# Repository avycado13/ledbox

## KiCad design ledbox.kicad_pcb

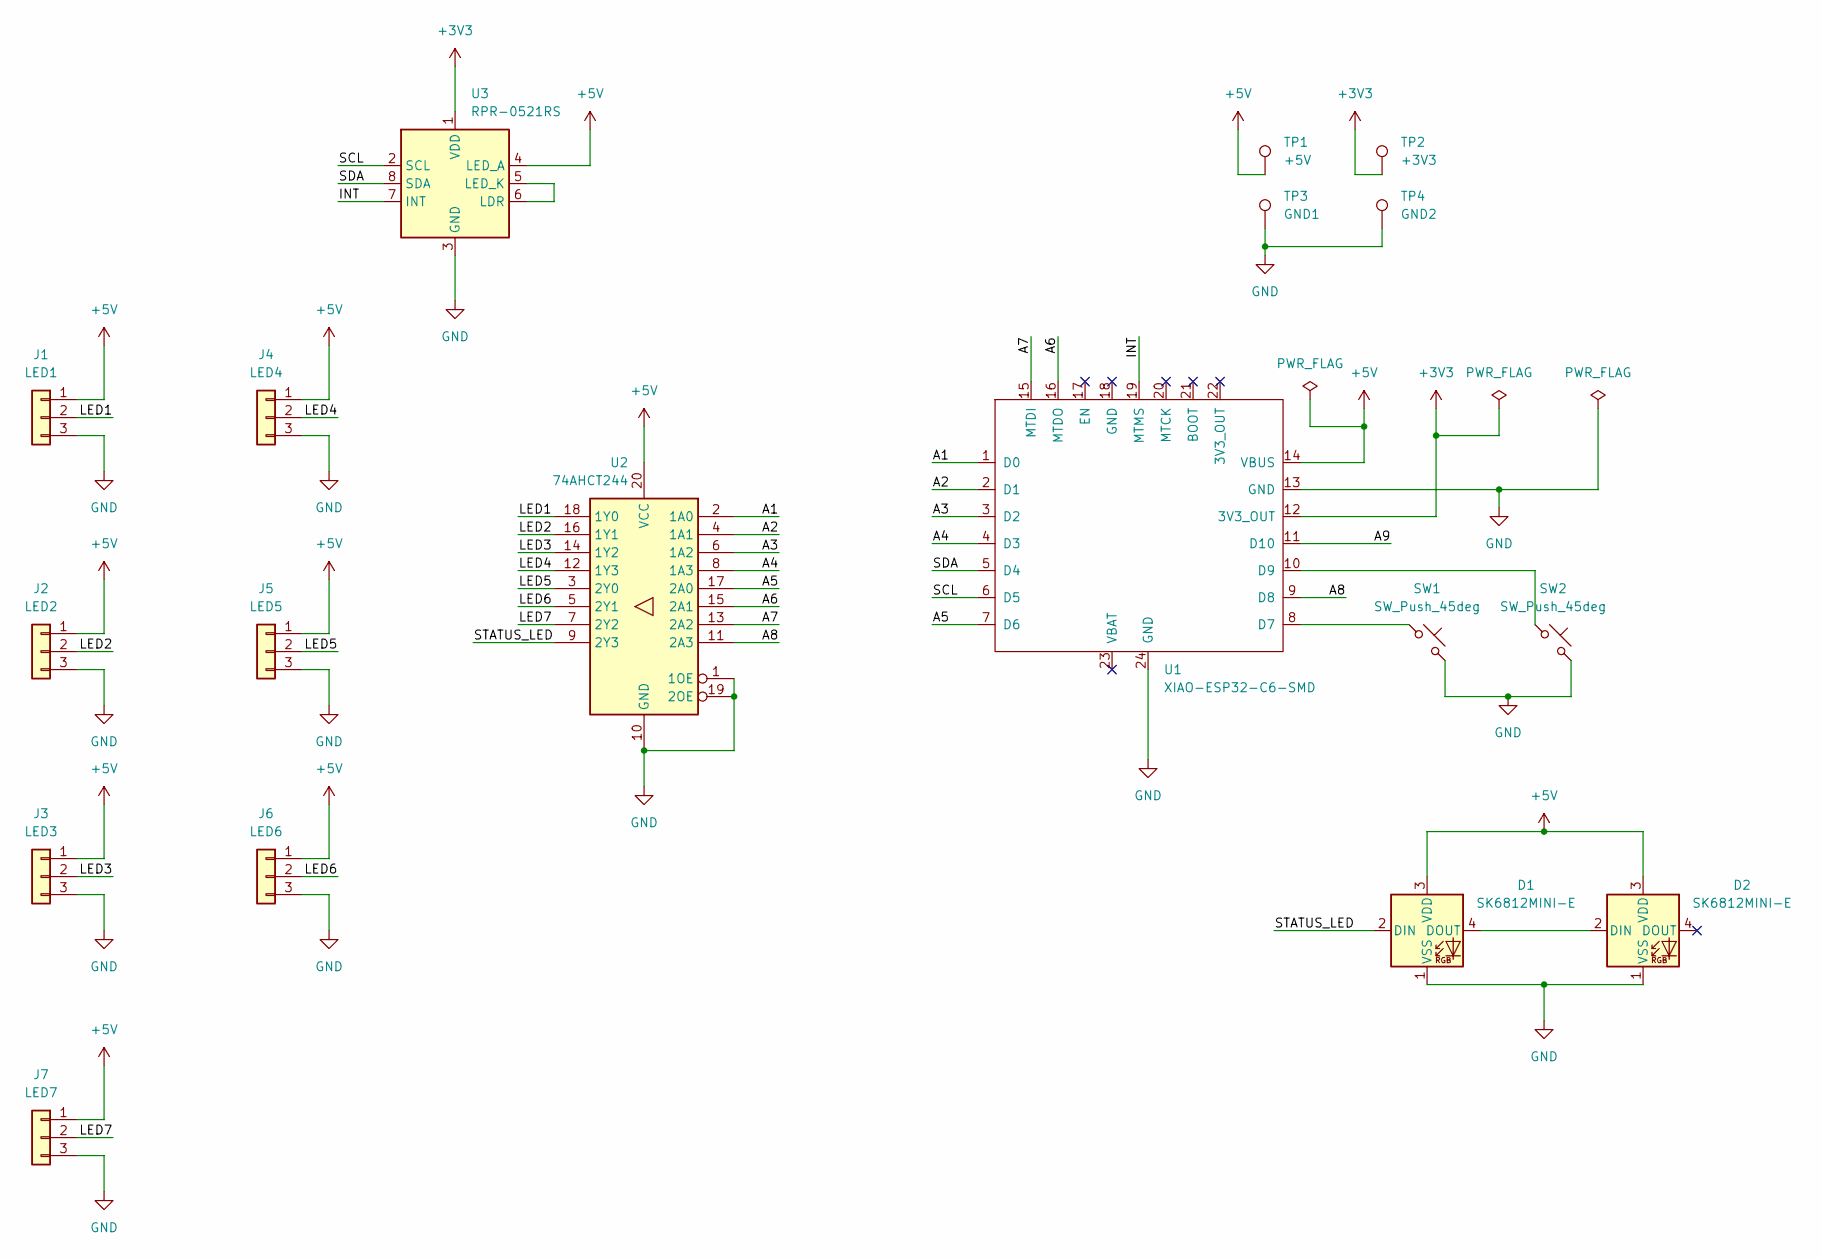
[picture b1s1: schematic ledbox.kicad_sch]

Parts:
D1, D2: SK6812MINI-E; LED_SK6812MINI-E_3.2x2.8mm_P1.5mm_ReverseMount
J1: LED1; PinHeader_1x03_P2.54mm_Horizontal
J2: LED2; PinHeader_1x03_P2.54mm_Horizontal
J3: LED3; PinHeader_1x03_P2.54mm_Horizontal
J4: LED4; PinHeader_1x03_P2.54mm_Horizontal
J5: LED5; PinHeader_1x03_P2.54mm_Horizontal
J6: LED6; PinHeader_1x03_P2.54mm_Horizontal
J7: LED7; PinHeader_1x03_P2.54mm_Horizontal
SW1, SW2: SW_Push_45deg; SW_SPST_PTS645Sx43SMTR92
TP1: +5V; TestPoint_Pad_D4.0mm
TP2: +3V3; TestPoint_Pad_D4.0mm
TP3: GND1; TestPoint_Pad_D4.0mm
TP4: GND2; TestPoint_Pad_D4.0mm
U1: XIAO-ESP32-C6-SMD
U2: 74AHCT244; TSSOP-20_4.4x6.5mm_P0.65mm
U3: RPR-0521RS; Rohm_RPR-0521RS

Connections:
+3V3: TP2.1 (1_1), U1.12 (3V3_OUT), U3.1 (VDD)
+5V: D1.3 (VDD), D2.3 (VDD), J1.1, J2.1, J3.1, J4.1, J5.1, J6.1, J7.1, TP1.1 (1_1), U1.14 (VBUS), U2.20 (VCC), U3.4 (LED_A)
/A1: U1.1 (D0), U2.2 (1A0)
/A2: U1.2 (D1), U2.4 (1A1)
/A3: U1.3 (D2), U2.6 (1A2)
/A4: U1.4 (D3), U2.8 (1A3)
/A5: U1.7 (D6), U2.17 (2A0)
/A6: U1.16 (MTDO), U2.15 (2A1)
/A7: U1.15 (MTDI), U2.13 (2A2)
/A8: U1.9 (D8), U2.11 (2A3)
/A9: U1.11 (D10)
/INT: U1.19 (MTMS), U3.7 (INT)
/LED1: J1.2, U2.18 (1Y0)
/LED2: J2.2, U2.16 (1Y1)
/LED3: J3.2, U2.14 (1Y2)
/LED4: J4.2, U2.12 (1Y3)
/LED5: J5.2, U2.3 (2Y0)
/LED6: J6.2, U2.5 (2Y1)
/LED7: J7.2, U2.7 (2Y2)
/SCL: U1.6 (D5), U3.2 (SCL)
/SDA: U1.5 (D4), U3.8 (SDA)
/STATUS_LED: D1.2 (DIN), U2.9 (2Y3)
GND: D1.1 (VSS), D2.1 (VSS), J1.3, J2.3, J3.3, J4.3, J5.3, J6.3, J7.3, SW1.2, SW2.2, TP3.1 (1_1), TP4.1 (1_1), U1.13 (GND), U1.24 (GND), U2.1 (1OE), U2.10 (GND), U2.19 (2OE), U3.3 (GND)
unnamed: D1.4 (DOUT), D2.2 (DIN)
unnamed: SW1.1, U1.8 (D7)
unnamed: SW2.1, U1.10 (D9)
unnamed: U3.5 (LED_K), U3.6 (LDR)

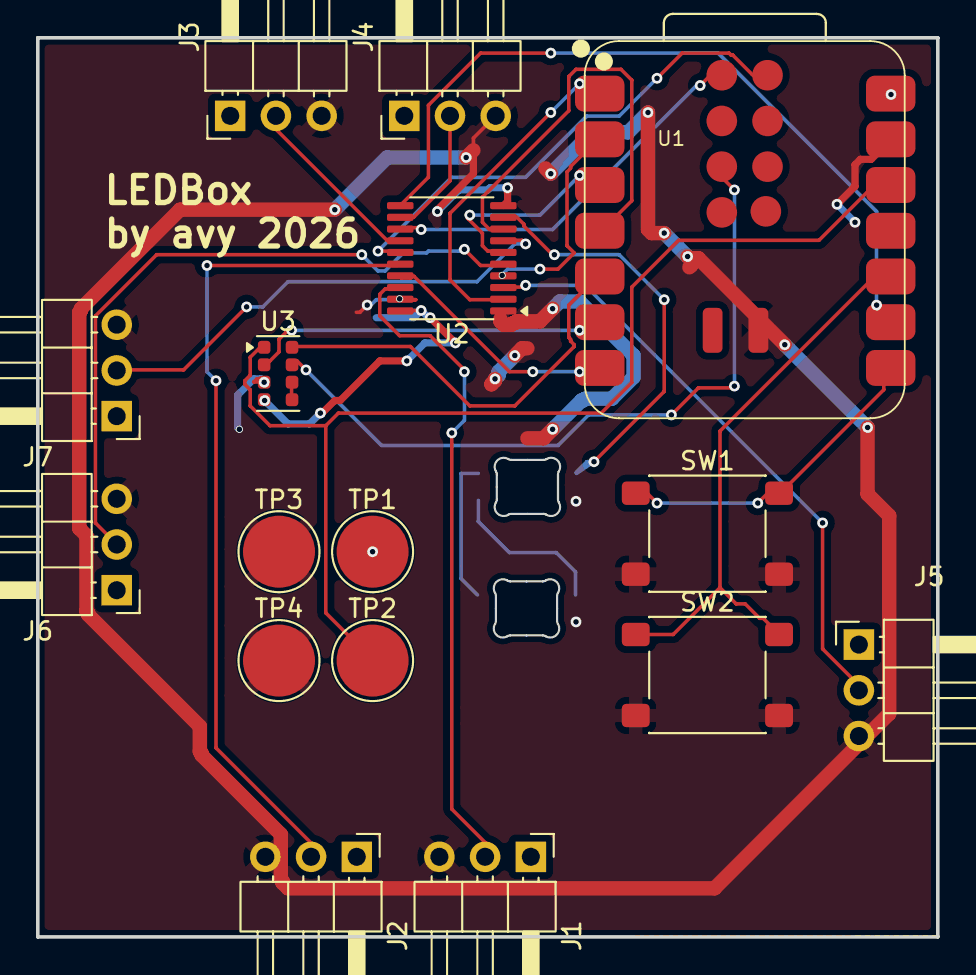
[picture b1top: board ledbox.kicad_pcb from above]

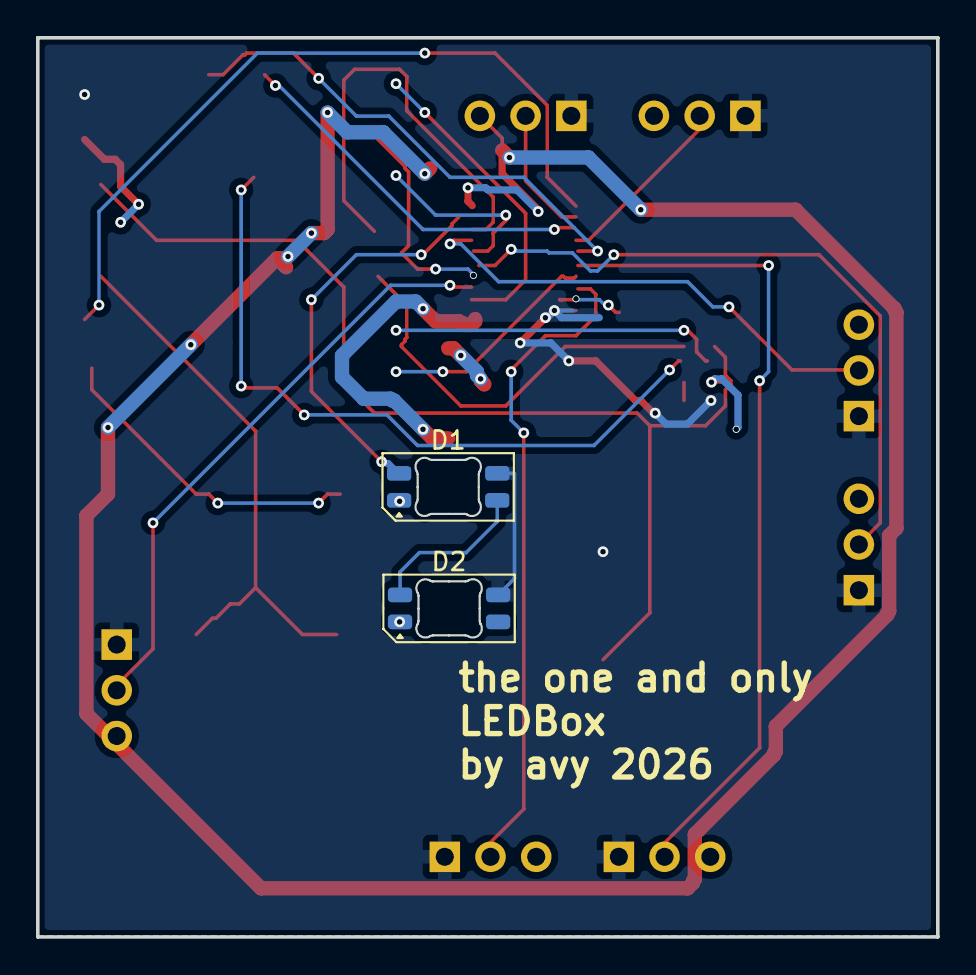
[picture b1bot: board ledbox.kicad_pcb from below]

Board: 2 copper layers, 50.0 x 50.0 mm, 18 parts (2 on the bottom side), 26 nets.

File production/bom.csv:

Designator,Footprint,Quantity,Value,LCSC Part #
"D1, D2",LED_SK6812MINI-E_3.2x2.8mm_P1.5mm_ReverseMount,2,SK6812MINI-E,
J1,PinHeader_1x03_P2.54mm_Horizontal,1,LED1,
J2,PinHeader_1x03_P2.54mm_Horizontal,1,LED2,
J3,PinHeader_1x03_P2.54mm_Horizontal,1,LED3,
J4,PinHeader_1x03_P2.54mm_Horizontal,1,LED4,
J5,PinHeader_1x03_P2.54mm_Horizontal,1,LED5,
J6,PinHeader_1x03_P2.54mm_Horizontal,1,LED6,
J7,PinHeader_1x03_P2.54mm_Horizontal,1,LED7,
"SW1, SW2",SW_SPST_PTS645Sx43SMTR92,2,SW_Push_45deg,
TP1,TestPoint_Pad_D4.0mm,1,+5V,
TP2,TestPoint_Pad_D4.0mm,1,+3V3,
TP3,TestPoint_Pad_D4.0mm,1,GND1,
TP4,TestPoint_Pad_D4.0mm,1,GND2,
U1,XIAO-ESP32-C6-SMD,1,XIAO-ESP32-C6-SMD,
U2,TSSOP-20_4.4x6.5mm_P0.65mm,1,74AHCT244,
U3,Rohm_RPR-0521RS,1,RPR-0521RS,
